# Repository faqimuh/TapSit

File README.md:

# TapSit
<div align="center">
  
</div>

# Sistem Pemilihan dan Pemantauan Tempat Duduk Berbasis RFID untuk Optimalisasi Industri F&B
<div align="justify">

Proyek ini bertujuan untuk mengembangkan sistem monitoring otomatis yang memantau ketersediaan tempat duduk di kafe dan restoran, menggunakan mikrokontroler ESP32 dan teknologi RFID. Sistem ini memungkinkan pelanggan untuk memilih meja dengan mengetuk kartu RFID, yang secara instan memperbarui status meja. Data yang dikumpulkan oleh cloud server disimpan dalam database lokal dan ditampilkan di monitor kasir, memungkinkan staf untuk melihat meja yang kosong dan terisi. Dengan demikian, sistem ini meningkatkan kenyamanan pelanggan dan efisiensi operasional, serta mengurangi waktu tunggu dan kesalahan.
[Slide Presentasi TapSit](https://www.canva.com/design/DAGSyjQpQgQ/xJnBZW7nx27bsGf2SDqeiA/edit?utm_content=DAGSyjQpQgQ&utm_campaign=designshare&utm_medium=link2&utm_source=sharebutton)
</div>

`IOT DAN JARINGAN SENSOR - PROGRAM STUDI TEKNIK ELEKTRONIKA - POLITEKNIK ELEKTRONIKA NEGERI SURABAYA`

`DOSEN PENGAMPU : Akhmad Hendriawan ST, MT`
`NIP. 197501272002121003`

## Manfaat
* Mengoptimalkan Pengelolaan Tempat Duduk
* Mengurangi Waktu Tunggu Pelanggan
* Meningkatkan Efisiensi Operasional
* Meningkatkan Kepuasan Pelanggan
* Mengurangi Kesalahan dalam Pengelolaan Tempat Duduk
* Memudahkan Rotasi Pelanggan
* Peningkatan Citra Modern dan Teknologi

## Keunggulan
* Pemantauan Real-time
* Otomatisasi Berbasis IoT
* Modular dan Skalabel
* Kompatibilitas dengan Infrastruktur Jaringan Lokal
* Visualisasi yang Jelas untuk Staf
* Penggunaan Teknologi RFID yang Cepat dan Aman
* Fleksibilitas Protokol Komunikasi

## Development Plan
### Tahun 1
* Monitoring kursi kosong dalam waktu nyata.
* Akses ke platform pemantauan tempat duduk berbasis cloud
* Notifikasi kursi kosong dalam waktu nyata.
* Laporan penggunaan kursi bulanan.
* Dukungan perangkat keras untuk 10 unit pembaca RFID.
### Tahun 2
* Pemantauan multi-lokasi (hingga 3 cabang).
* Laporan penggunaan kursi mingguan dan bulanan.
* Integrasi dengan aplikasi reservasi pihak ketiga.
* Dukungan perangkat keras untuk 30 unit pembaca RFID.
### Tahun 3
* Analitik lanjutan dan laporan custom sesuai permintaan.
* Dukungan pemantauan untuk hingga 10 lokasi.
* Sistem pemesanan kursi langsung untuk pelanggan melalui aplikasi mobile.
* Dukungan perangkat keras untuk 50 unit pembaca RFID.

## Teammates
<div align="center">

| No. | Nama                | NRP            | Pembagian Tugas                                                  | GitHub                                 |
| :--:| :------------------:| :-------------:| :--------------------------------------------------------------:| :------------------------------------: |
| 1   | Muhammad Faqidin    | 2122600013     | Project Manager, Publikasi melalui Github                       | [GitHub](https://github.com/faqimuh) |
| 2   | Ahmad Zen Ashari    | 2122600009     | Hardware, Desain Skematik dan Hardware, Publikasi melalui Github| [GitHub](https://github.com/ahmadzenashari) |
| 3   | Fadlan Surya        | 2122600024     | Software, Mengatur Koneksi Hardware ke Broker, Publikasi melalui Github | [GitHub](https://github.com/fadlansuryanindita) |
| 4   | Adib Tantowi        | 2122600001     | UI/UX Designer, Membuat tampilan Web Server, Publikasi melalui Github | [GitHub](https://github.com/AdibTantowi) |
| 5   | Rizka Sugiharto     | 2122600008     | Data Analyst, Mengambil data dari Broker ke DataBase, Publikasi melalui Github | [GitHub](https://github.com/Rizka-sgh) |
| 6   | M Lukman Al Khakim  | 2122600010     | Procurement Product, Proses Perakitan dan Soldering, Publikasi melalui Github | [GitHub](https://github.com/2122600010-M-Lukman-Alkhakim) |

</div>

# Daftar Isi
- [Desain Produk](#Desain-Produk)
- [Diagram Arsitektur Sistem](#Diagram-Arsitektur-Sistem)
- [Hardware](#Hardware)
    * [Rangkaian Skematik](#Rangkaian-Skematik)
    * [Pin I/O](#Pinout)
    * [Layout PCB](#Layout-PCB)
- [Software](#Software)
  * [Aktifasi SSL/TLS di Broker HiveMQ CLoud](MQTT/MQTT.md)
  * [Membuat Cloud di AWS Console (EC2)](Cloud/VPS.md)
  * [Koneksi Broker dengan Database Menggunakan Node-Red](Database/progres.md)
- [Rincian Biaya](#Rincian-Biaya)

# Desain Produk

<div align="center">

 ![Tampilan Produk 0][def0]
 ![Tampilan Produk 1][def1]
 ![Tampilan Produk 2][def2]

[def0]: /assets/Desain1.png
[def1]: /assets/Desain2.png
[def2]: /assets/Desain3.png
[Download File 3D](https://www.thingiverse.com/thing:6816870) <br>
[File 3D](https://github.com/faqimuh/TapSit/tree/main/Hardware%20Development/Desain3D)
</div>

## Uploud Casing di thingivers

<div align="center">

https://www.thingiverse.com/thing:6816870
</div>

## Diagram Block

# Diagram Arsitektur Sistem

# Hardware
## Rangkaian Skematik
<div align = center>

</div>

 ## Layout PCB
 <div align = center>

<p> Menggunakan PCB 2 Layer </p>
<a href="https://github.com/faqimuh/TapSit/tree/main/Hardware%20Development/LayoutPCB">FILE PCB</a>
</div>

  ## Pinout yang Dipakai

Pin GPIO34 | untuk data input baterai<br>
Pin GPIO26 | untuk indikator LED<br>
Pin GPIO27 | untuk indikator LED<br>
Pin GPIO13 | untuk input interrupt<br>
Pin GPIO14 | untuk output buzzer<br>
Pin MISO   | untuk RFID <br>
Pin MOSI   | untuk RFID<br>
Pin SCK    | untuk RFID<br>
Pin SDA    | untuk RFID<br>
Pin RST    | untuk RFID<br>
Pin 3,3V   | untuk input tegangan<br>
Pin GND    | untuk ground<br>

# Software
Selamat datang di proyek ini. Berikut adalah beberapa panduan yang mungkin Anda butuhkan:
- [Aktifasi SSL/TLS di Broker HiveMQ CLoud](MQTT/MQTT.md)
- [Membuat Cloud di AWS Console (EC2)](Cloud/VPS.md)
- [Koneksi Broker dengan Database Menggunakan Node-Red](Database/progres.md)

# Rincian Biaya

| No  | Item                   | Jumlah | Harga   | Total   |Link|
|-----|------------------------|--------|---------|---------|-----|
| 1   | ESP32 Devkitc 32D      | 1      | 66.900  | 66.900  |[Buy](https://s.shopee.co.id/g7zNegvfe) |
| 2   | Buzzer SMD 8530 3V     | 1      | 4.000   | 4.000   |[Buy](https://www.tokopedia.com/marnov/buzzer-smd-8530-3v-16r-8-5-3mm-piezo-mini-aktif-pasif?extParamsrc%3Dshop%26whid%3D225282) |
| 3   | LED SMD 1206           | 2      | 140     | 280     |[Buy](https://tokopedia.link/4pipX6fPrNb)|
| 4   | RFID MRFC 522          | 1      | 14.000  | 14.000  |[Buy](https://s.shopee.co.id/sIaWPa9R)         |
| 5   | Resistor SMD 1206      | 3      | 150     | 450     |[Buy](https://tokopedia.link/CMivhgmPrNb)    |
| 6   | Etching Papan PCB      | 1      | 8.000   | 8.000   |   |
| 7   | 3D print casing        | 1      | 20.000  | 20.000  |     |
| 8   | TP4056 1A 5V Lithium   | 1      | 4.000   | 4.000   |[Buy](https://www.tokopedia.com/isee/tp4056-1a-5v-lithium-lipo-18650-battery-charging-usb-type-c-proteksi) |
| 9   | Lithium 2500mah 3.7V   | 1      | 37.000  | 37.000  |[Buy](https://id.shp.ee/LSUCxvz)                |
|     |                        |        | **TOTAL** | 154.630 |

# Tampilan UI/UX
<div align="center">
  <h3><span style="color:#0078D7;">Tampilan Index</span></h3>
   <p><i>Menampilkan informasi ketersediaan meja secara real-time, membantu pengguna mengetahui meja yang kosong atau terisi.</i></p>
  
</div>

<div align="center">
  <h3>Tampilan Login </h3>
  <p><i>Halaman login untuk mengamankan akses ke web admin, dirancang khusus agar hanya karyawan atau pemilik yang dapat masuk .</i></p>
  
</div>

<div align="center">
  <h3> Tampilan Admin </h3>
  <p><i>
    Tampilan ini dirancang khusus untuk karyawan atau pemilik yang memiliki akses ke halaman admin. Melalui halaman ini, mereka dapat memantau kondisi meja secara real-time, termasuk informasi apakah meja kosong atau terisi, serta melihat status RFID di setiap meja. Selain itu, halaman ini terdapat pengecekan tingkat baterai alat RFID, yang dikategorikan dalam tiga kondisi: aman, hampir habis, atau habis, guna memastikan perangkat berfungsi dengan optimal. Admin juga memiliki kemampuan untuk mengganti password login sebagai langkah menjaga keamanan akses sistem.
  </i></p>
  </i></p>

  <a href="https://github.com/faqimuh/TapSit/tree/main/Interface%20UI/UX">FILE UI-UX</a>
</div>

# Cara Penggunaan 

https://github.com/user-attachments/assets/884f3dd7-7e4f-4ce1-bf2d-9252606a5dd6

1. Pastikan perangkat dalam kondisi menyala dan telah berhasil terhubung dengan jaringan Wi-Fi untuk memastikan kelancaran proses komunikasi data.
2. Pada tampilan web server, sistem akan menampilkan status setiap meja; meja yang belum terisi akan ditandai dengan warna hijau, sementara meja yang telah terisi akan ditandai dengan warna merah, memungkinkan pemantauan kondisi secara visual.
3. Tempelkan kartu RFID yang sudah terdaftar pada perangkat untuk mengaktifkan proses pengenalan identitas melalui sensor.
4. Data dari kartu RFID yang ditempelkan akan secara otomatis dikirim dan disimpan dalam database untuk tujuan pencatatan dan pemantauan.
5. Pada perangkat atau meja yang sama, sistem database hanya akan memperbarui informasi terkait kondisi terakhir RFID serta status pemantauan baterai untuk efisiensi penyimpanan dan pemrosesan data.
6. Setelah kartu RFID berhasil ditempelkan pada perangkat, tampilan pada web server akan secara otomatis diperbarui, menunjukkan bahwa meja tersebut telah terisi, berkat registrasi yang telah terjadi melalui perangkat.

Untuk memberikan gambaran yang lebih jelas, video ini akan menunjukkan seluruh proses, mulai dari pengaktifan hingga penggunaan alat dalam berbagai kondisi, sehingga Anda bisa memahami manfaat dan efisiensi alat kami yang dapat diakses pada link [VIDIO IKLAN](https://youtu.be/MPJk97POcxs?si=4I_-UE-o9XQQt0bo)

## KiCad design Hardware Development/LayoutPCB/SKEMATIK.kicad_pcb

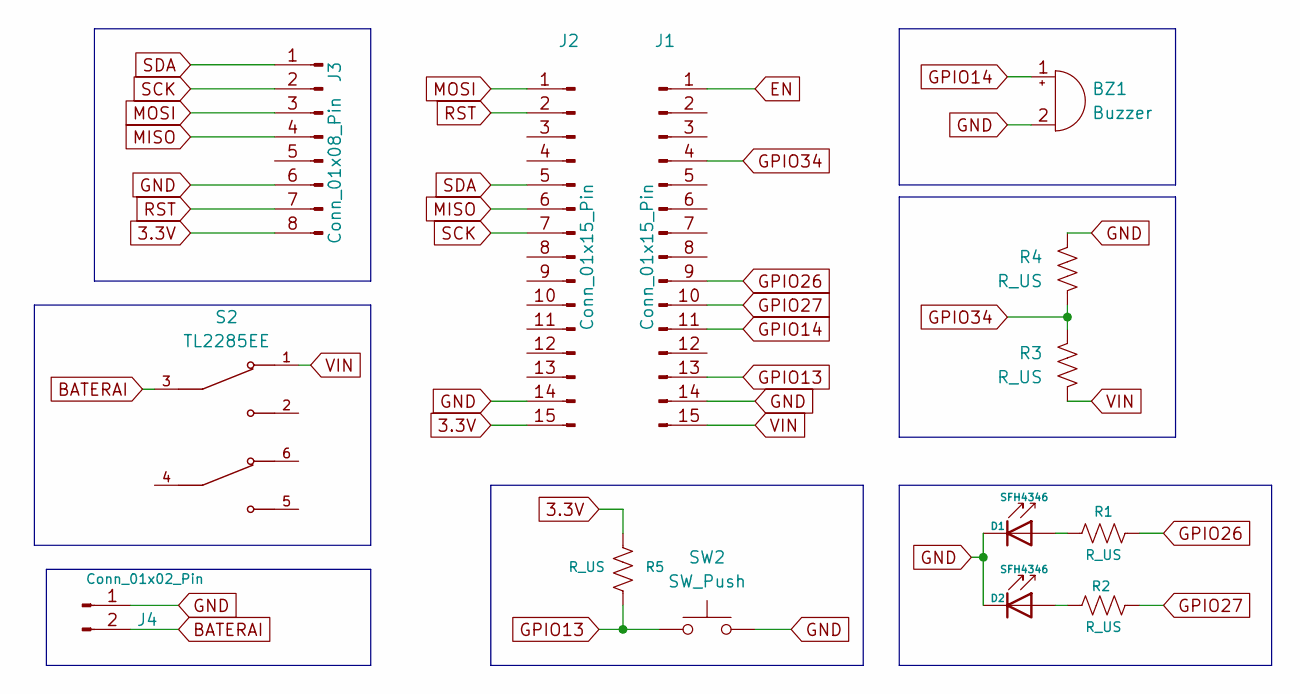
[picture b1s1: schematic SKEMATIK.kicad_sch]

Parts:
BZ1: Buzzer; PUIAudio_SMT_0825_S_4_R
D1, D2: SFH4346; LED_D3.0mm_IRBlack
J1, J2: Conn_01x15_Pin; PinHeader_1x15_P2.54mm_Vertical
J3: Conn_01x08_Pin; PinHeader_1x08_P2.54mm_Vertical
J4: Conn_01x02_Pin; JST_EH_B2B-EH-A_1x02_P2.50mm_Vertical
R1, R2, R3, R4, R5: R_US; R_1206_3216Metric
S2: TL2285EE; SW_TL2285EE; PARTREV B
SW2: SW_Push; SW_PUSH_6mm

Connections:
3.3V: J2.15, J3.8, R5.1
BATERAI: J4.2, S2.3
EN: J1.1
GND: BZ1.2 (-), D1.1 (K), D2.1 (K), J1.14, J2.14, J3.6, J4.1, R4.1, SW2.2
GPIO13: J1.13, R5.2, SW2.1
GPIO14: BZ1.1 (+), J1.11
GPIO26: J1.9, R1.2
GPIO27: J1.10, R2.2
GPIO34: J1.4, R3.1, R4.2
MISO: J2.6, J3.4
MOSI: J2.1, J3.3
unnamed: D1.2 (A), R1.1
unnamed: D2.2 (A), R2.1
RST: J2.2, J3.7
SCK: J2.7, J3.2
SDA: J2.5, J3.1
VIN: J1.15, R3.2, S2.1

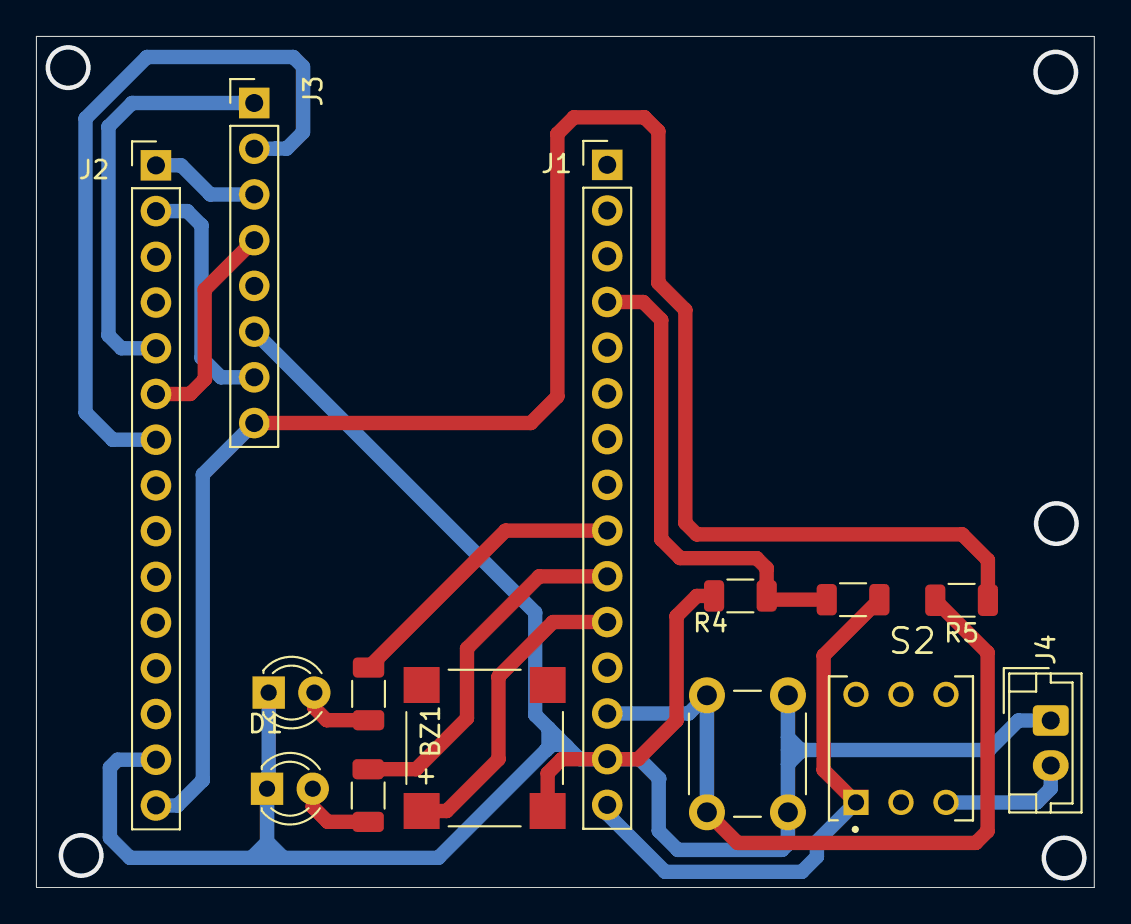
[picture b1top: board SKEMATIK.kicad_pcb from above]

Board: 2 copper layers, 58.8 x 47.3 mm, 14 parts (0 on the bottom side), 16 nets.

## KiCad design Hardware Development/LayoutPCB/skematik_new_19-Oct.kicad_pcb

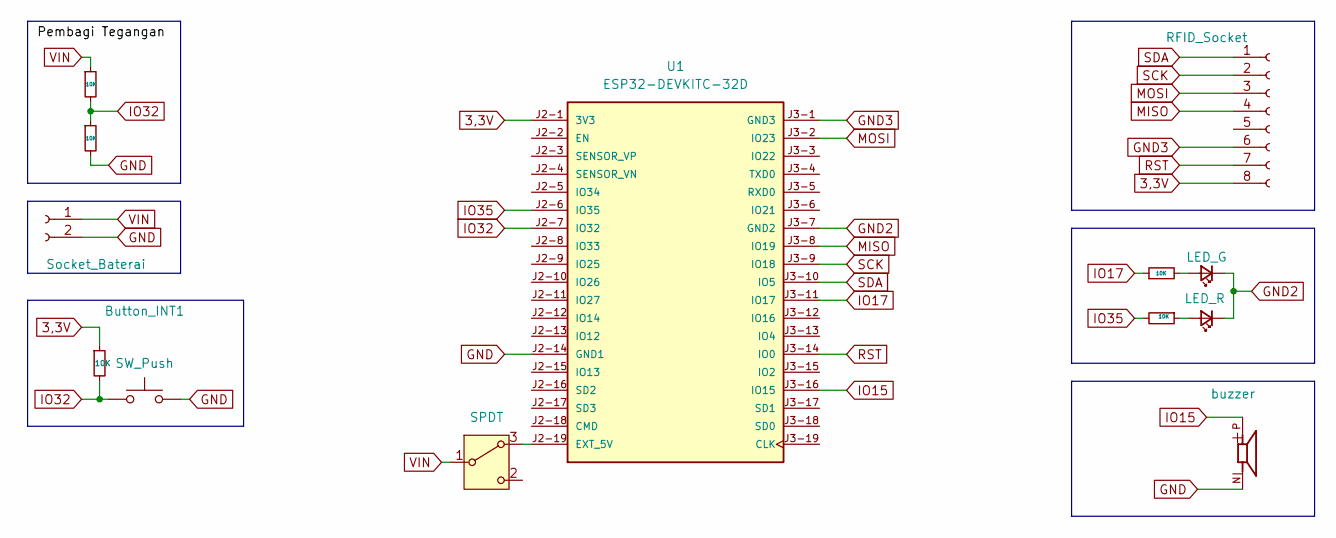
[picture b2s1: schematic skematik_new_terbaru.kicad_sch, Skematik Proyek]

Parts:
Button_INT1: SW_Push; SW_PUSH_6mm
D1: LED_R; LED_D4.0mm
D2: LED_G; LED_D4.0mm
J1: RFID_Socket; PinHeader_1x08_P2.54mm_Vertical
J2: Socket_Baterai; PinHeader_1x02_P2.54mm_Vertical
LS1: buzzer; CUI_CMT-8540S-SMT
R1, R2, R3, R4, R5: 10K; R_0201_0603Metric
SW3: SPDT; SW_ATE1D-2M3-10-Z
U1: ESP32-DEVKITC-32D; MODULE_ESP32-DEVKITC-32D; PARTREV V4

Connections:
3,3V: J1.8, R5.1, U1.J2-1 (3V3)
GND: Button_INT1.2, J2.2, LS1.N, R2.2, U1.J2-14 (GND1)
GND2: D1.1 (K), D2.1 (K), U1.J3-7 (GND2)
GND3: J1.6, U1.J3-1 (GND3)
IO15: LS1.P, U1.J3-16 (IO15)
IO17: R4.1, U1.J3-11 (IO17)
IO32: Button_INT1.1, R1.2, R2.1, R5.2, U1.J2-7 (IO32)
IO35: R3.2, U1.J2-6 (IO35)
MISO: J1.4, U1.J3-8 (IO19)
MOSI: J1.3, U1.J3-2 (IO23)
unnamed: D1.2 (A), R3.1
unnamed: D2.2 (A), R4.2
unnamed: SW3.3 (A), U1.J2-19 (EXT_5V)
RST: J1.7, U1.J3-14 (IO0)
SCK: J1.2, U1.J3-9 (IO18)
SDA: J1.1, U1.J3-10 (IO5)
VIN: J2.1, R1.1, SW3.1 (B)

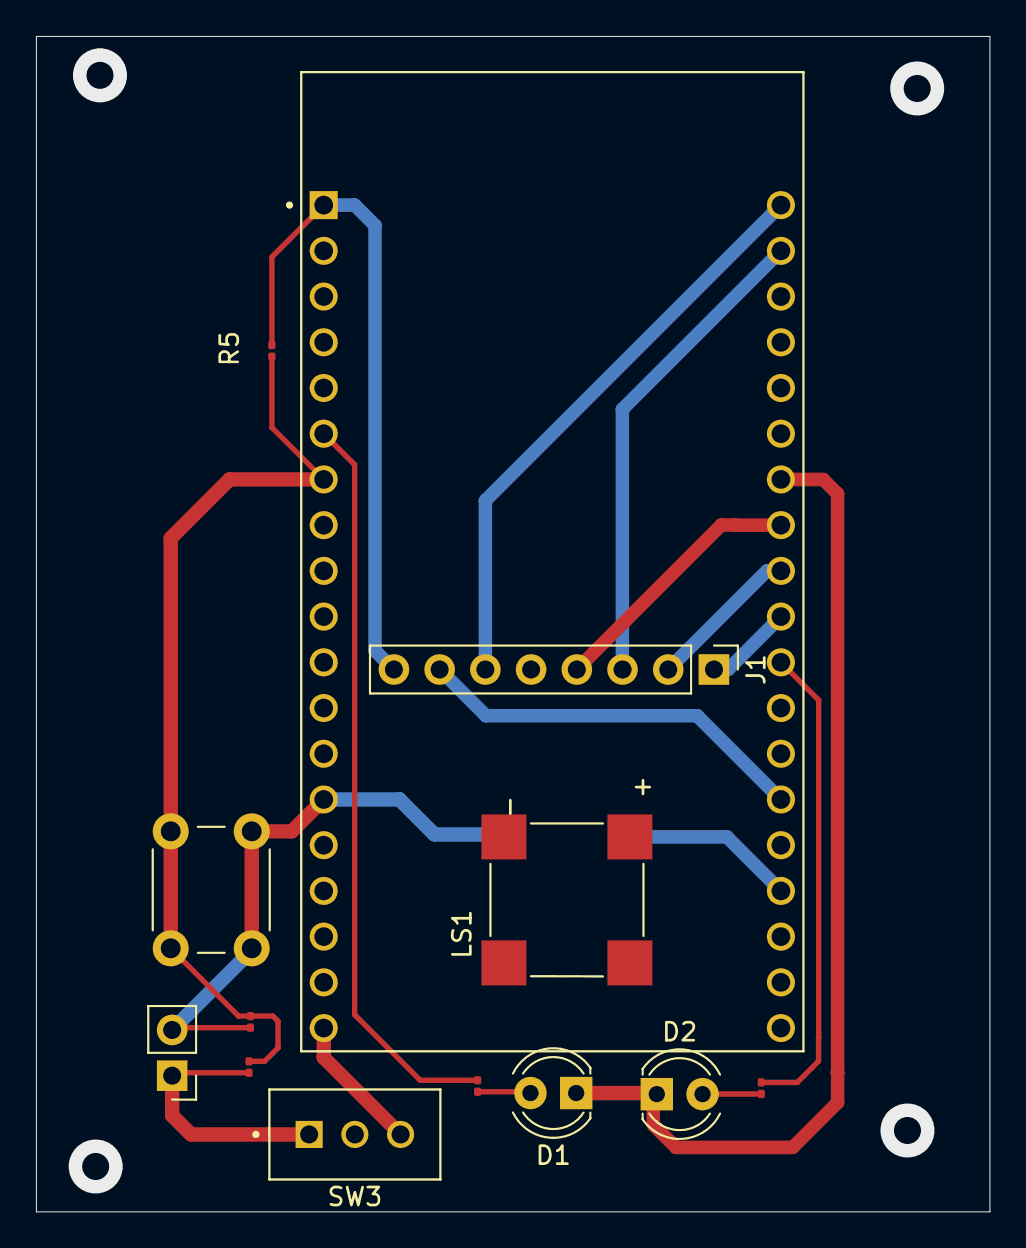
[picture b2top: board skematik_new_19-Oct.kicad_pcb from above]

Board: 2 copper layers, 53.0 x 65.3 mm, 13 parts (0 on the bottom side), 17 nets.

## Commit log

2024-10-07 Create Hardware
2024-10-07 assets
2024-10-07 Create Logo
2024-10-08 Create Skematik
2024-10-08 Create prototype
2024-10-08 ganti nama
2024-10-09 penambahan folder
2024-10-09 test1
2024-10-09 IKI COBA COMMIT
2024-10-09 test2
2024-10-09 ytty
2024-10-09 test0
2024-10-09 cobabos
2024-10-09 cobaaaa
2024-10-09 skematik
2024-10-10 detail baru
2024-10-10 data baru
2024-10-11 coba bang
2024-10-11 Update Data
2024-10-11 coba
2024-10-11 progres1
2024-10-11 update baru
2024-10-11 updatebaru
2024-10-11 COBAA
2024-10-11 baru
2024-10-11 Updateterbaru
2024-10-11 skematik.png
2024-10-11 Tambahkan file Interface UI/UX/pages/
2024-10-11 databaru
2024-10-12 pembuatan-design-skematik-rangkaian
2024-10-12 data
2024-10-12 updateMD
2024-10-12 Desain Skematik
2024-10-12 edit readme 1
2024-10-12 bismilah
2024-10-12 bismillah2
2024-10-12 bismillah3
2024-10-12 detail data
2024-10-13 edit hardware
2024-10-13 delete
2024-10-13 Penjelasan skematik dan pcb ditaruh di readmed
2024-10-13 perbarui2 readme
2024-10-13 review
2024-10-13 program pengiriman data ke broker
2024-10-14 video_simulasi
2024-10-15 update skematik baru
2024-10-20 Revert "Merge pull request #57 from faqimuh/13-pembuatan-design-skematik-rang…"
2024-10-20 Update firmware;penambahan pengiriman sampling level battrey
2024-10-20 berkas sch
2024-10-20 desain pcb hasil revisi
2024-10-20 Desain full product
2024-10-21 uploud foto
2024-10-21 Update firmware PENAMBAHAN WIFI MANAGER DAN LevEL BaTerai
2024-10-21 Revert "Update firmware;penambahan pengiriman sampling level battrey"
    This reverts commit 2a96c7f016f7a8f791cd55a126fc6d39b2ad3498.
2024-10-23 perbarui file skematik,layout,dan tampilan 3D PCB
2024-10-26 finishing desain hardware
2024-10-26 finishing desain hardware tadi vidio tak bisa muncul
2024-10-26 maaf commit ketiga kalinya, ada typo sedikit yang telah saya perbaiki
2024-10-27 Update Readme aktifasi SSL di HiveMQ1
2024-10-28 UPDATE FIRMWARE, Custom Parameter dan RFID reader
2024-10-28 UPDATE MD untuk penjelasan LIBRAY
2024-10-28 penambahan anggota team
2024-10-29 saya uploud desain 3D semuanya
2024-11-01 penambahan diagram block system TapSit
2024-11-02 perbaikan diagram sistem
2024-11-02 saya sudah uploud di thingverse,sehingga file bisa dicetak di 3D print
2024-11-03 update stackholder
2024-11-06 perbarui link thinkverse
2024-11-09 Pengaplikasian BUZZER
2024-11-09 Pembuatan markdown penjelasan program
2024-11-09 Penambahan video testing(trial and error
2024-11-09 update perapisan readme
2024-11-10 memasukkan gambar tampilan TapSit
2024-11-10 edit tampilan tambahan
2024-11-10 edit tampilan sofware
2024-11-10 edit progres database
2024-11-10 edit tampilan teammates
2024-11-10 link ytb dan cara penggunaan
2024-11-10 Tambahan alur penggunaan untuk customer
2024-11-10 membuat tutorial how to create cloud vps
2024-11-10 Update VPS.md video tutorial
2024-11-10 edit foto anggota
2024-11-10 upluad code
2024-11-11 Update folder build, Font, Img , Js , Music-Files
2024-11-11 Update README.md daftar isi
2024-11-17 update tampilan
2024-11-24 Add files via upload
    Ui-Ux
